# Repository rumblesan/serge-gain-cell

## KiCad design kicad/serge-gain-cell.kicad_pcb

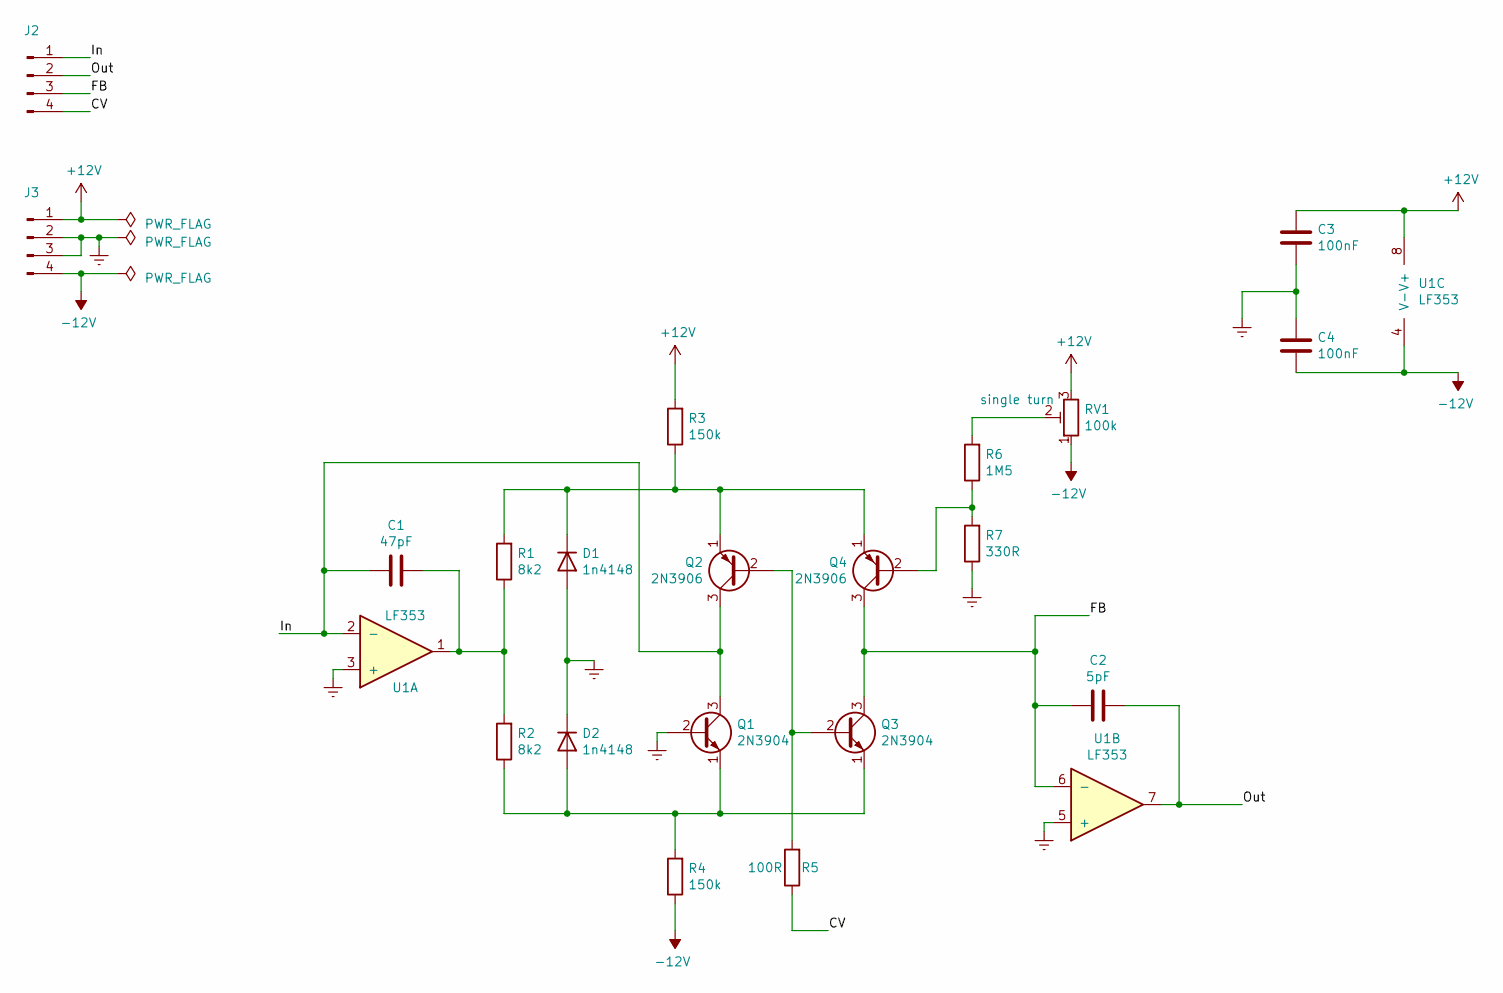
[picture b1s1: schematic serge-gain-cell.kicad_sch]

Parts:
C1: 47pF; C_Rect_L7.0mm_W2.5mm_P5.00mm; Tolerance 5%
C2: 5pF; C_Rect_L7.0mm_W2.5mm_P5.00mm; Tolerance 5%
C3, C4: 100nF; C_Rect_L7.0mm_W2.5mm_P5.00mm; Tolerance 5%
D1, D2: 1n4148; D_DO-35_SOD27_P2.54mm_Vertical_AnodeUp
J2, J3: Conn_01x04_Pin; PinHeader_1x04_P2.54mm_Vertical
Q1, Q3: 2N3904; TO-92_Inline_Wide
Q2, Q4: 2N3906; TO-92_Inline_Wide
R1, R2: 8k2; R_Axial_DIN0207_L6.3mm_D2.5mm_P2.54mm_Vertical; Tolerance 1%
R3, R4: 150k; R_Axial_DIN0207_L6.3mm_D2.5mm_P2.54mm_Vertical; Tolerance 1%
R5: 100R; R_Axial_DIN0207_L6.3mm_D2.5mm_P2.54mm_Vertical; Tolerance 1%
R6: 1M5; R_Axial_DIN0207_L6.3mm_D2.5mm_P2.54mm_Vertical; Tolerance 1%
R7: 330R; R_Axial_DIN0207_L6.3mm_D2.5mm_P2.54mm_Vertical; Tolerance 1%
RV1: 100k; Potentiometer_THT_Bourns_3306P_Vertical
U1: LF353; DIP-8_W7.62mm_Socket

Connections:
+12V: C3.2, J3.1, R3.2, RV1.3, U1.8 (V+)
-12V: C4.1, J3.4, R4.1, RV1.1, U1.4 (V-)
/CV: J2.4, R5.1
/FB: C2.2, J2.3, Q3.3 (C), Q4.3 (C), U1.6 (-)
/In: C1.2, J2.1, Q1.3 (C), Q2.3 (C), U1.2 (-)
/Out: C2.1, J2.2, U1.7
GNDREF: C3.1, C4.2, D1.2 (A), D2.1 (K), J3.2, J3.3, Q1.2 (B), R7.1, U1.3 (+), U1.5 (+)
unnamed: C1.1, R1.1, R2.2, U1.1
unnamed: D1.1 (K), Q2.1 (E), Q4.1 (E), R1.2, R3.1
unnamed: D2.2 (A), Q1.1 (E), Q3.1 (E), R2.1, R4.2
unnamed: Q2.2 (B), Q3.2 (B), R5.2
unnamed: Q4.2 (B), R6.1, R7.2
unnamed: R6.2, RV1.2

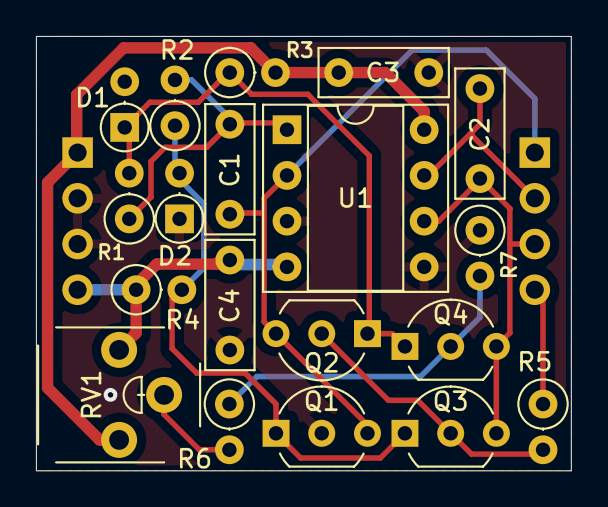
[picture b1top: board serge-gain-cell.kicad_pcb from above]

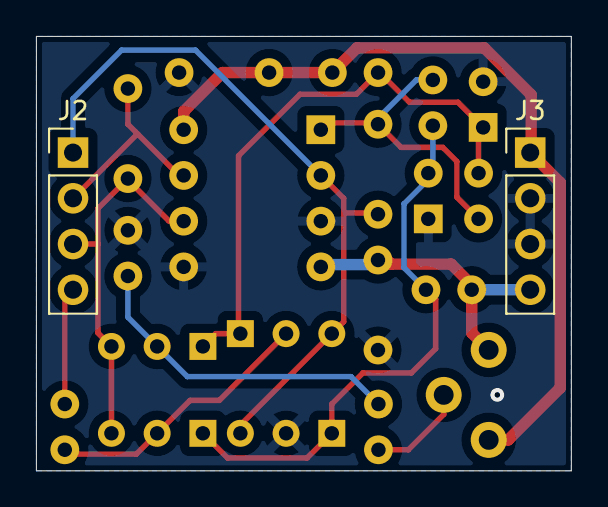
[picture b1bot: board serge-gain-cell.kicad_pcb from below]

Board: 2 copper layers, 29.7 x 24.1 mm, 21 parts (2 on the bottom side), 13 nets.

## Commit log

2023-07-19 Initial commit with rev01
2024-09-16 Updating to newer kicad version
2024-09-16 Adding basic analysis data

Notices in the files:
kicad/serge-gain-cell.kicad_pcb:
creativecommons.org/licenses/by/4.0
License: CC BY 4.0
